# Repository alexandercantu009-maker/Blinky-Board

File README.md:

# Blinky Board – Cybertruck Edition

A blinky board I designed in KiCad for Hack Club Twisted. A 555 timer clocks a CD4017 counter, which lights 10 LEDs one after another along the truck's body. The board is shaped like a Cybertruck, with wheels and window art on the silkscreen.

## Schematic

## How it works
- The NE555P runs as an astable oscillator. The 50 kΩ potentiometer (RV2) changes the speed.
- Each clock pulse moves the CD4017 to its next output (Q0 to Q9), so the 10 LEDs light in sequence.
- Power comes from a 9 V battery on a battery clip, plugged into the 2-pin header J1 (red wire to pin 1 = positive, black wire to pin 2 = GND).

## Bill of materials

| Component | Ref | Qty | Unit cost | Line cost | Buy |
|---|---|---|---|---|---|
| 1 µF 50 V electrolytic capacitor | C1 | 1 | $0.025 | $0.02 | [C62934](https://www.lcsc.com/product-detail/C62934.html) |
| 0.01 µF (10 nF) capacitor | C2 | 1 | $0.036 | $0.04 | [C249157](https://www.lcsc.com/product-detail/C249157.html) |
| 5 mm LED | D1-D10 | 10 | $0.024 | $0.24 | [C2895480](https://www.lcsc.com/product-detail/C2895480.html) |
| 2-pin 2.54 mm power header | J1 | 1 | $0.013 | $0.01 | [C492401](https://www.lcsc.com/product-detail/C492401.html) |
| 1 kΩ resistor | R1 | 1 | $0.007 | $0.01 | [C713997](https://www.lcsc.com/product-detail/C713997.html) |
| 470 Ω resistor | R2 | 1 | $0.010 | $0.01 | [C58592](https://www.lcsc.com/product-detail/C58592.html) |
| 50 kΩ trimmer potentiometer | RV2 | 1 | $0.178 | $0.18 | [C118912](https://www.lcsc.com/product-detail/C118912.html) |
| NE555P timer (DIP-8) | U1 | 1 | $0.228 | $0.23 | [C46749](https://www.lcsc.com/product-detail/C46749.html) |
| CD4017BE counter (DIP-16) | U2 | 1 | $0.519 | $0.52 | [C34519](https://www.lcsc.com/product-detail/C34519.html) |
| 9 V battery clip (off-board, plugs into J1) | – | 1 | $0.160 | $0.16 | [Tayda A-5266](https://www.taydaelectronics.com/connectors-sockets/battery-connectors-holders/9v-9-volt-battery-clip-connector-snap-black-color.html) |
| **Total** | | | | **$1.42** | |

Prices are approximate LCSC listings (the battery clip is from Tayda) for one board's worth of parts. The 9 V battery itself is not in the BOM, so any standard 9 V battery works. LCSC sells some parts in minimum quantities, so an actual order costs more.

The same list, with footprints and part numbers, is in [`BOM.csv`](BOM.csv).

## Files
- `Blinky Board.kicad_pro`, `.kicad_sch`, `.kicad_pcb`: KiCad project, schematic, and PCB
- `Gerbers.zip`: manufacturing files
- `BOM.csv`: bill of materials with costs and links
- `Blinky Board.png`: 3D render
- `schematic.png`: schematic image

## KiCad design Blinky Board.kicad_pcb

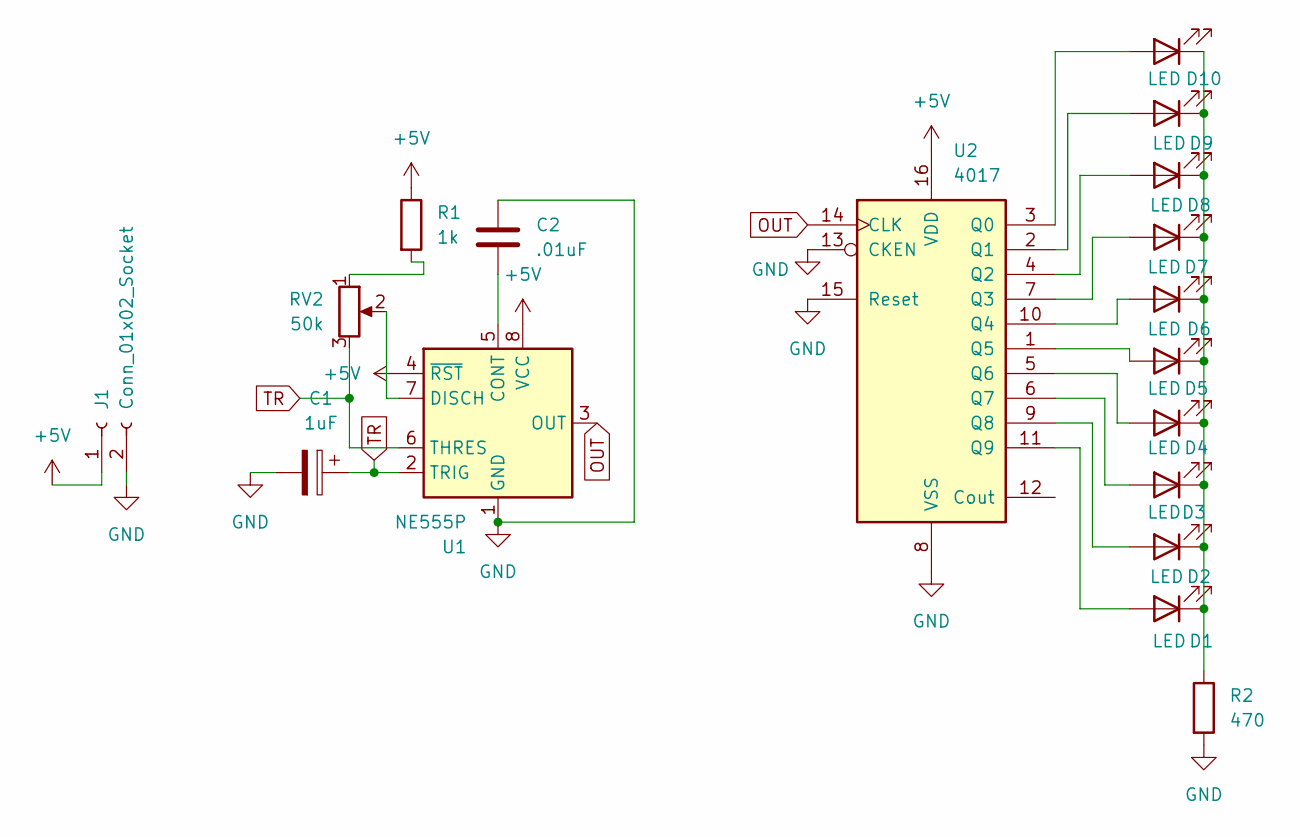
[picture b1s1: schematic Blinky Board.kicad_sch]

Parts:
C1: 1uF; CP_Radial_D5.0mm_P2.00mm
C2: .01uF; C_Disc_D5.0mm_W2.5mm_P5.00mm
D1, D2, D3, D4, D5, D6, D7, D8, D9, D10: LED; LED_D5.0mm
J1: Conn_01x02_Socket; PinHeader_1x02_P2.54mm_Vertical
R1: 1k; R_Axial_DIN0207_L6.3mm_D2.5mm_P7.62mm_Horizontal
R2: 470; R_Axial_DIN0207_L6.3mm_D2.5mm_P7.62mm_Horizontal
RV2: 50k; Potentiometer_Bourns_3299W_Vertical
U1: NE555P; DIP-8_W7.62mm
U2: 4017; DIP-16_W7.62mm

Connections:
+5V: J1.1, R1.1, U1.4 (~RST), U1.8 (VCC), U2.16 (VDD)
GND: C1.2, C2.1, J1.2, R2.2, U1.1 (GND), U2.8 (VSS), U2.13 (CKEN), U2.15 (Reset)
unnamed: D1.2 (A), U2.11 (Q9)
unnamed: D1.1 (K), D2.1 (K), D3.1 (K), D4.1 (K), D5.1 (K), D6.1 (K), D7.1 (K), D8.1 (K), D9.1 (K), D10.1 (K), R2.1
unnamed: D2.2 (A), U2.9 (Q8)
unnamed: D3.2 (A), U2.6 (Q7)
unnamed: D4.2 (A), U2.5 (Q6)
unnamed: D5.2 (A), U2.1 (Q5)
unnamed: D6.2 (A), U2.10 (Q4)
unnamed: D7.2 (A), U2.7 (Q3)
unnamed: D8.2 (A), U2.4 (Q2)
unnamed: D9.2 (A), U2.2 (Q1)
unnamed: D10.2 (A), U2.3 (Q0)
unnamed: R1.2, RV2.1
unnamed: C2.2, U1.5 (CONT)
unnamed: RV2.2, U1.7 (DISCH)
OUT: U1.3 (OUT), U2.14 (CLK)
TR: C1.1, RV2.3, U1.2 (TRIG), U1.6 (THRES)

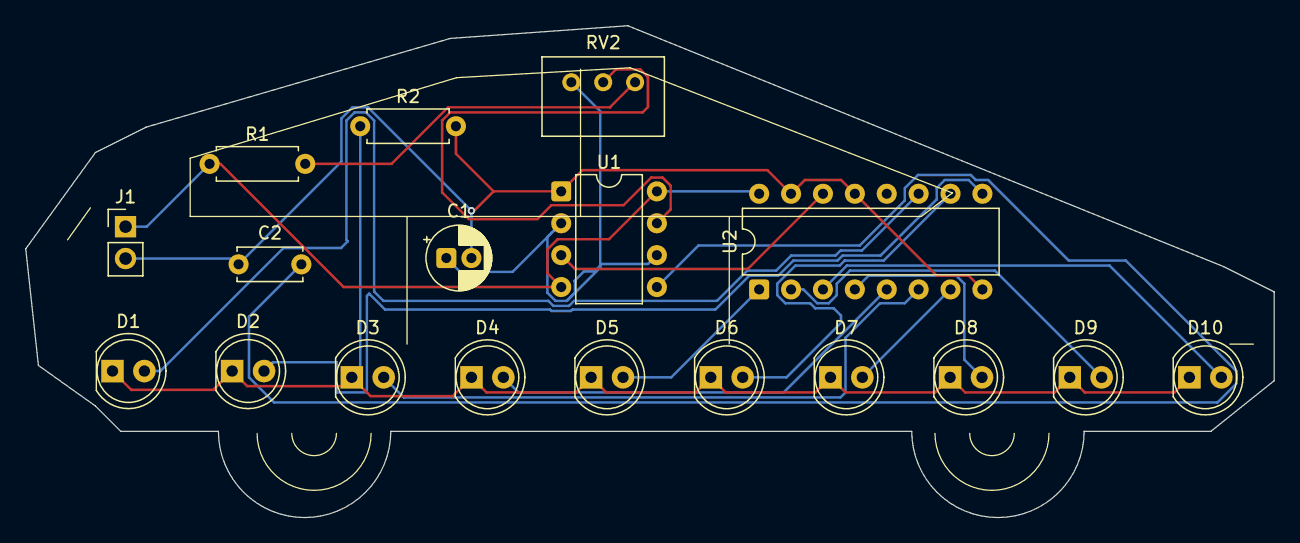
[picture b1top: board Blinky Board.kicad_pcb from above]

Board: 2 copper layers, 99.4 x 39.2 mm, 18 parts (0 on the bottom side), 18 nets.

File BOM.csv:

"Reference","Qty","Value","DNP","Exclude from BOM","Exclude from Board","Exclude from Simulation","Exclude from Position Files","Footprint","Datasheet","Manufacturer Part","LCSC Part #","Unit Cost (USD)","Line Cost (USD)","Link"
"C1","1","1uF","","","","","${EXCLUDE_FROM_POS_FILES}","Capacitor_THT:CP_Radial_D5.0mm_P2.00mm","","KF010M050C110A","C62934","0.0249","0.0249","https://www.lcsc.com/product-detail/C62934.html"
"C2","1",".01uF","","","","","${EXCLUDE_FROM_POS_FILES}","Capacitor_THT:C_Disc_D5.0mm_W2.5mm_P5.00mm","","N09F1B103MN0B0S0N0","C249157","0.0360","0.0360","https://www.lcsc.com/product-detail/C249157.html"
"D1,D2,D3,D4,D5,D6,D7,D8,D9,D10","10","LED","","","","","${EXCLUDE_FROM_POS_FILES}","LED_THT:LED_D5.0mm","","XL-502UWC","C2895480","0.0244","0.2440","https://www.lcsc.com/product-detail/C2895480.html"
"J1","1","Conn_01x02_Socket","","","","","${EXCLUDE_FROM_POS_FILES}","Connector_PinHeader_2.54mm:PinHeader_1x02_P2.54mm_Vertical","","PZ254V-11-02P","C492401","0.0130","0.0130","https://www.lcsc.com/product-detail/C492401.html"
"R1","1","1k","","","","","${EXCLUDE_FROM_POS_FILES}","Resistor_THT:R_Axial_DIN0207_L6.3mm_D2.5mm_P7.62mm_Horizontal","","MF1/4W-1KΩ±1%T52","C713997","0.0070","0.0070","https://www.lcsc.com/product-detail/C713997.html"
"R2","1","470","","","","","${EXCLUDE_FROM_POS_FILES}","Resistor_THT:R_Axial_DIN0207_L6.3mm_D2.5mm_P7.62mm_Horizontal","","MFR0W4F4700A50","C58592","0.0100","0.0100","https://www.lcsc.com/product-detail/C58592.html"
"RV2","1","50k","","","","","${EXCLUDE_FROM_POS_FILES}","Potentiometer_THT:Potentiometer_Bourns_3299W_Vertical","","3296X-1-503","C118912","0.1780","0.1780","https://www.lcsc.com/product-detail/C118912.html"
"U1","1","NE555P","","","","","${EXCLUDE_FROM_POS_FILES}","Package_DIP:DIP-8_W7.62mm","http://www.ti.com/lit/ds/symlink/ne555.pdf","NE555P","C46749","0.2282","0.2282","https://www.lcsc.com/product-detail/C46749.html"
"U2","1","4017","","","","","${EXCLUDE_FROM_POS_FILES}","Package_DIP:DIP-16_W7.62mm","http://www.intersil.com/content/dam/Intersil/documents/cd40/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","CD4017BE","C34519","0.5193","0.5193","https://www.lcsc.com/product-detail/C34519.html"
"9V battery clip (off-board)","1","9V battery clip","","","","","","N/A (wires plug into J1)","","9V battery clip with wire leads","Tayda A-5266 (not LCSC)","0.1600","0.1600","https://www.taydaelectronics.com/connectors-sockets/battery-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"
"TOTAL (parts for one board)","","","","","","","","","","","","","1.42",""
